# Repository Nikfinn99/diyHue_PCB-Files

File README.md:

# Moved to [Nikfinn99/PCB_Designs](https://github.com/Nikfinn99/PCB_Designs)
# in this new repo are also more Designs available

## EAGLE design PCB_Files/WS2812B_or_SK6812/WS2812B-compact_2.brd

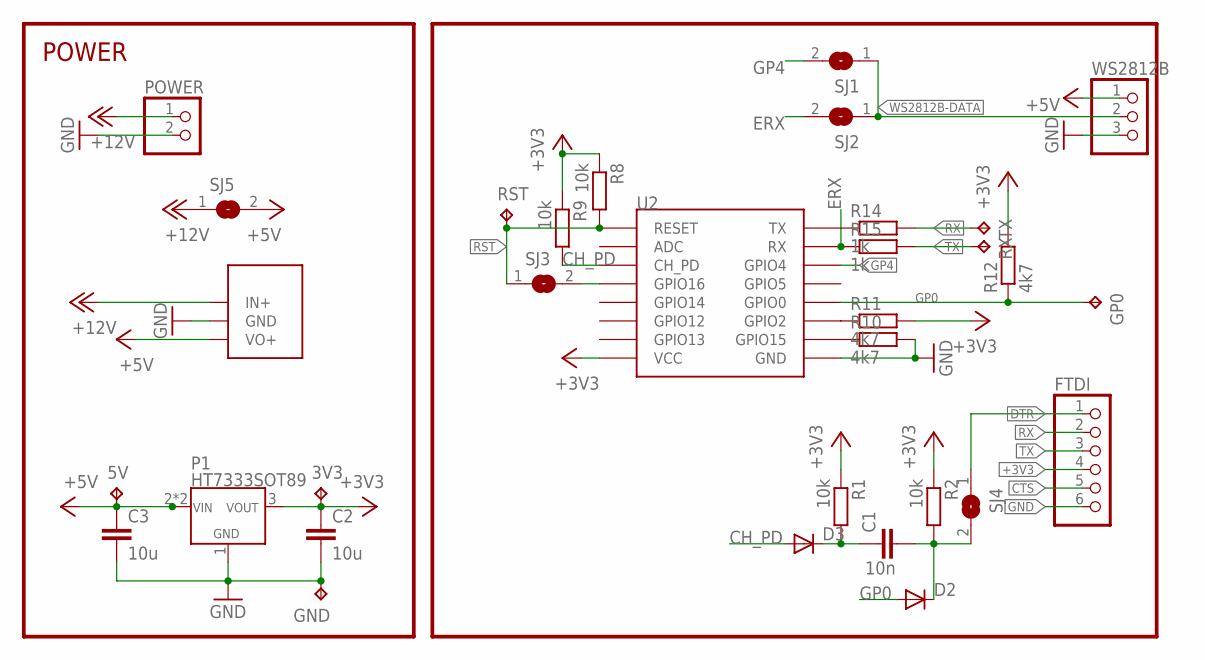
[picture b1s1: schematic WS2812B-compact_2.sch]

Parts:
3V3, 5V: TPB1,27; B1,27
C1: 10n; C0805
C2, C3: 10u; C0805
D2, D3: DIODE-MINIMELF; MINIMELF
FTDI: PINHD-1X06_2.54-S; 1X06-S
GND: TPB1,27; B1,27
GP0: TPB1,27; B1,27
P1: HT7333SOT89; SOT89
POWER: PINHD-1X2; 1X02
R1, R2, R8, R9: 10k; R0805
R10, R11, R12: 4k7; R0805
R14, R15: 1k; R0805
RST: TPB1,27; B1,27
RX: TPB1,27; B1,27
SJ1, SJ2, SJ3, SJ4, SJ5: SJ
TX: TPB1,27; B1,27
U2: ESP12SMD; ESP12-SMD
U$1: BUCK_CONVERTER_TE818_VAR
WS2812B: PINHD-1X03_2.54-S; 1X03-S

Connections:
+3V3: 3V3.TP, C2.1, FTDI.4, P1.3 (VOUT), R1.1, R2.1, R8.1, R9.1, R11.2, R12.2, U2.VCC
+5V: 5V.TP, C3.1, P1.2 (VIN), P1.2@1 (VIN), SJ5.2, U$1.VO+, WS2812B.1
+12V: POWER.1, SJ5.1, U$1.IN+
CH_PD: D3.A, R9.2, U2.CH_PD
CTS: FTDI.5
DTR: FTDI.1, SJ4.1
ERX: R15.1, SJ2.2, U2.RXD0 (RX)
GND: C2.2, C3.2, FTDI.6, GND.TP, P1.1 (GND), POWER.2, R10.2, U2.GND, U$1.GND, WS2812B.3
GP0: D2.A, GP0.TP, R12.1, U2.GPIO0
GP4: SJ1.2, U2.GPIO4
unnamed: C1.2, D2.C, R2.2, SJ4.2
unnamed: C1.1, D3.C, R1.2
unnamed: R10.1, U2.GPIO15
unnamed: R11.1, U2.GPIO2
unnamed: SJ3.2, U2.GPIO16
unnamed: R14.1, U2.TXD0 (TX)
RST: R8.2, RST.TP, SJ3.1, U2.RESET
RX: FTDI.2, R14.2, TX.TP
TX: FTDI.3, R15.2, RX.TP
WS2812B-DATA: SJ1.1, SJ2.1, WS2812B.2

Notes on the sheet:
POWER

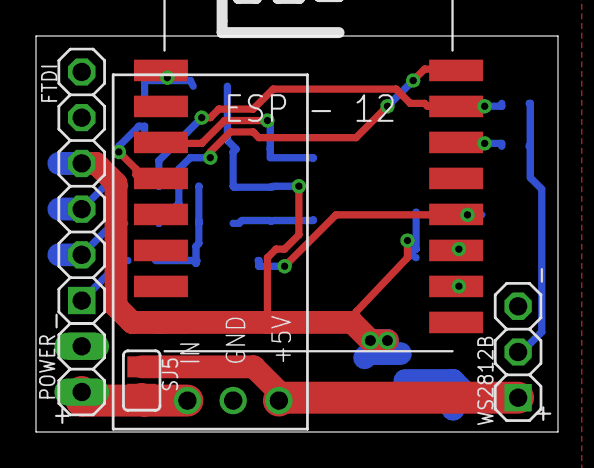
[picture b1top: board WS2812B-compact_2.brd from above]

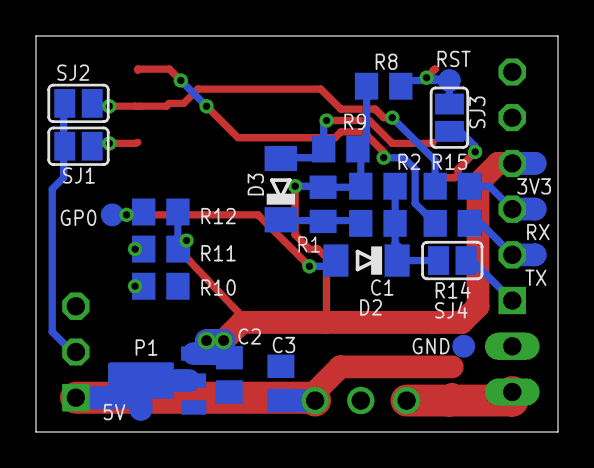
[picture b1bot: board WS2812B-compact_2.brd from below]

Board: 2 copper layers, 29.0 x 22.0 mm, 32 parts (26 on the bottom side), 19 nets.

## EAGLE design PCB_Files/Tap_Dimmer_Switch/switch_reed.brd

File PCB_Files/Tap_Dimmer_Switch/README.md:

## This design is currently under development

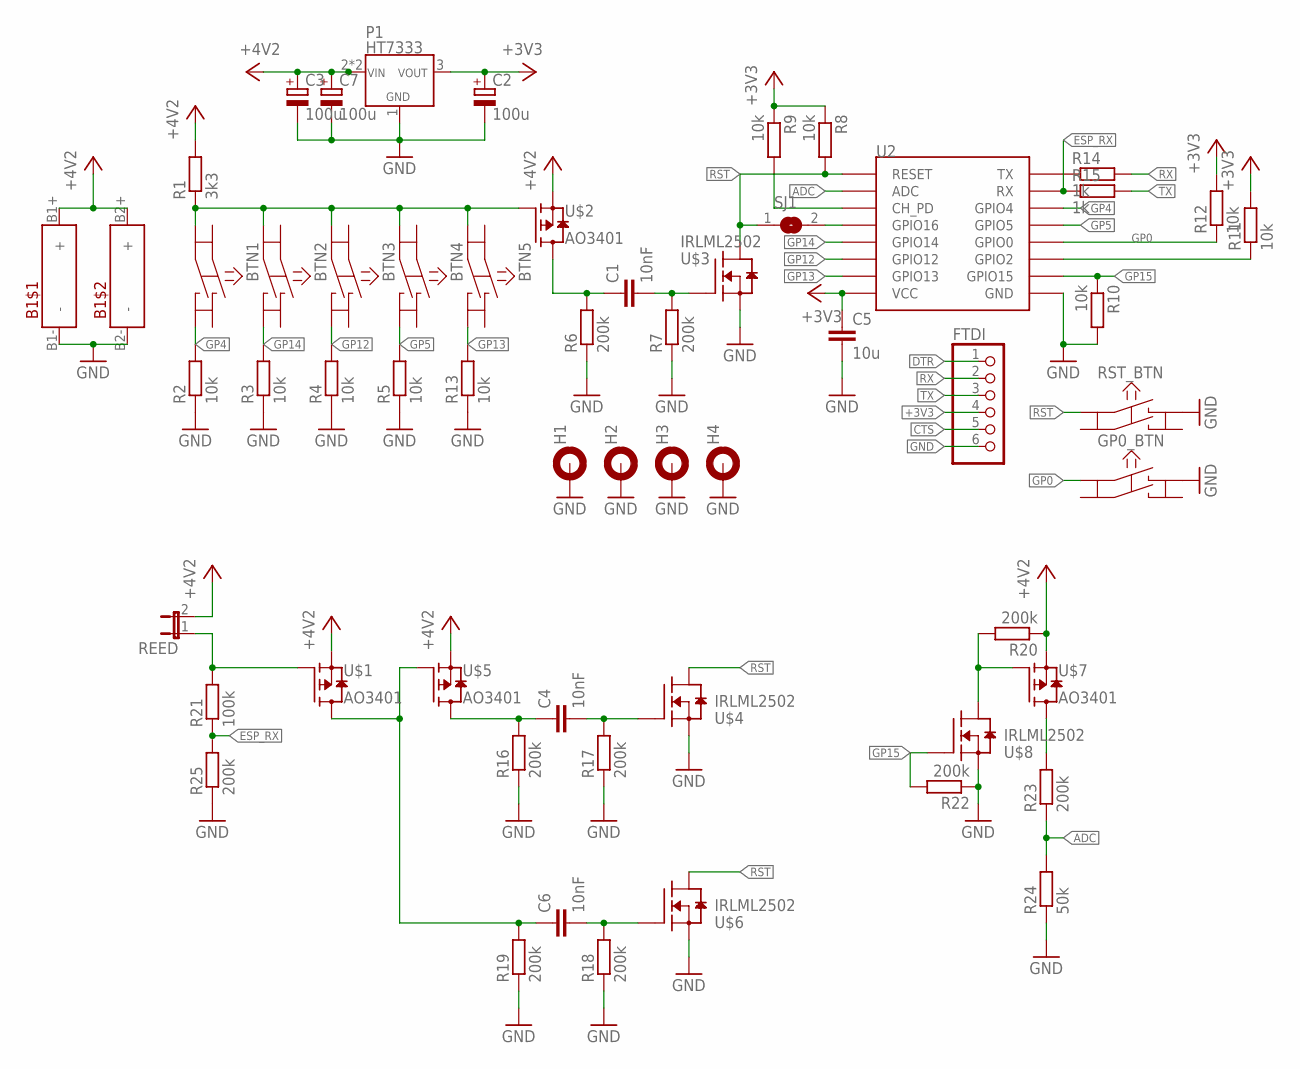
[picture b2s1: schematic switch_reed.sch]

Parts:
B1: 18650_2X; 18650_HOLDER
BTN1, BTN2, BTN3, BTN4, BTN5: KSM611A
C1, C4, C6: 10nF; C0805
C2, C3, C7: 100u; E5-8,5
C5: 10u; C1206
FTDI: PINHD-1X06_2.54-S; 1X06-S
GP0_BTN: KSM611A
H1, H2, H3, H4: MOUNT-PAD-ROUND3.2; 3,2-PAD
P1: HT7333; SOT89
R1: 3k3; R0805
R2, R3, R4, R5, R8, R9, R10, R11, R12, R13: 10k; R0805
R6, R7, R16, R17, R18, R19, R20, R22, R23, R25: 200k; R0805
R14, R15: 1k; R0805
R21: 100k; R0805
R24: 50k; R0805
REED: JP1E; JP1
RST_BTN: KSM611A
SJ1: SJ
U2: ESP12SMD; ESP12-SMD
U$1, U$2, U$5, U$7: AO3401; SOT23
U$3, U$4, U$6, U$8: IRLML2502; SOT23

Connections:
+3V3: C2.+, C5.1, FTDI.4, P1.3 (VOUT), R8.1, R9.1, R11.2, R12.2, U2.VCC
+5V: B1.B1+ (+), B1.B2+ (+), C3.+, C7.+, P1.2 (VIN), P1.2@1 (VIN), R1.2, R20.1, REED.2, U$1.2 (S), U$2.2 (S), U$5.2 (S), U$7.2 (S)
ADC: R23.1, R24.2, U2.ADC
CTS: FTDI.5
DTR: FTDI.1
ESP_RX: R15.1, R21.1, R25.2, U2.RXD0 (RX)
GND: B1.B1- (-), B1.B2- (-), C2.-, C3.-, C5.2, C7.-, FTDI.6, GP0_BTN.B, H1.B3,2, H2.B3,2, H3.B3,2, H4.B3,2, P1.1 (GND), R2.1, R3.1, R4.1, R5.1, R6.1, R7.1, R10.2, R13.1, R16.1, R17.1, R18.1, R19.1, R22.1, R24.1, R25.1, RST_BTN.B, U2.GND, U$3.2 (S), U$4.2 (S), U$6.2 (S), U$8.2 (S)
GP0: GP0_BTN.A, R12.1, U2.GPIO0
GP4: BTN1.D, R2.2, U2.GPIO4
GP5: BTN4.D, R5.2, U2.GPIO5
GP12: BTN3.D, R4.2, U2.GPIO12
GP13: BTN5.D, R13.2, U2.GPIO13
GP14: BTN2.D, R3.2, U2.GPIO14
GP15: R10.1, R22.2, U2.GPIO15, U$8.1 (G)
unnamed: SJ1.2, U2.GPIO16
unnamed: R9.2, U2.CH_PD
unnamed: C1.2, R7.2, U$3.1 (G)
unnamed: R11.1, U2.GPIO2
unnamed: R14.1, U2.TXD0 (TX)
unnamed: C1.1, R6.2, U$2.3 (D)
unnamed: BTN1.C, BTN2.C, BTN3.C, BTN4.C, BTN5.C, R1.1, U$2.1 (G)
unnamed: C6.1, R19.2, U$1.3 (D), U$5.1 (G)
unnamed: C4.1, R16.2, U$5.3 (D)
unnamed: C4.2, R17.2, U$4.1 (G)
unnamed: C6.2, R18.2, U$6.1 (G)
unnamed: R20.2, U$7.1 (G), U$8.3 (D)
unnamed: R23.2, U$7.3 (D)
unnamed: R21.2, REED.1, U$1.1 (G)
RST: R8.2, RST_BTN.A, SJ1.1, U2.RESET, U$3.3 (D), U$4.3 (D), U$6.3 (D)
RX: FTDI.2, R14.2
TX: FTDI.3, R15.2

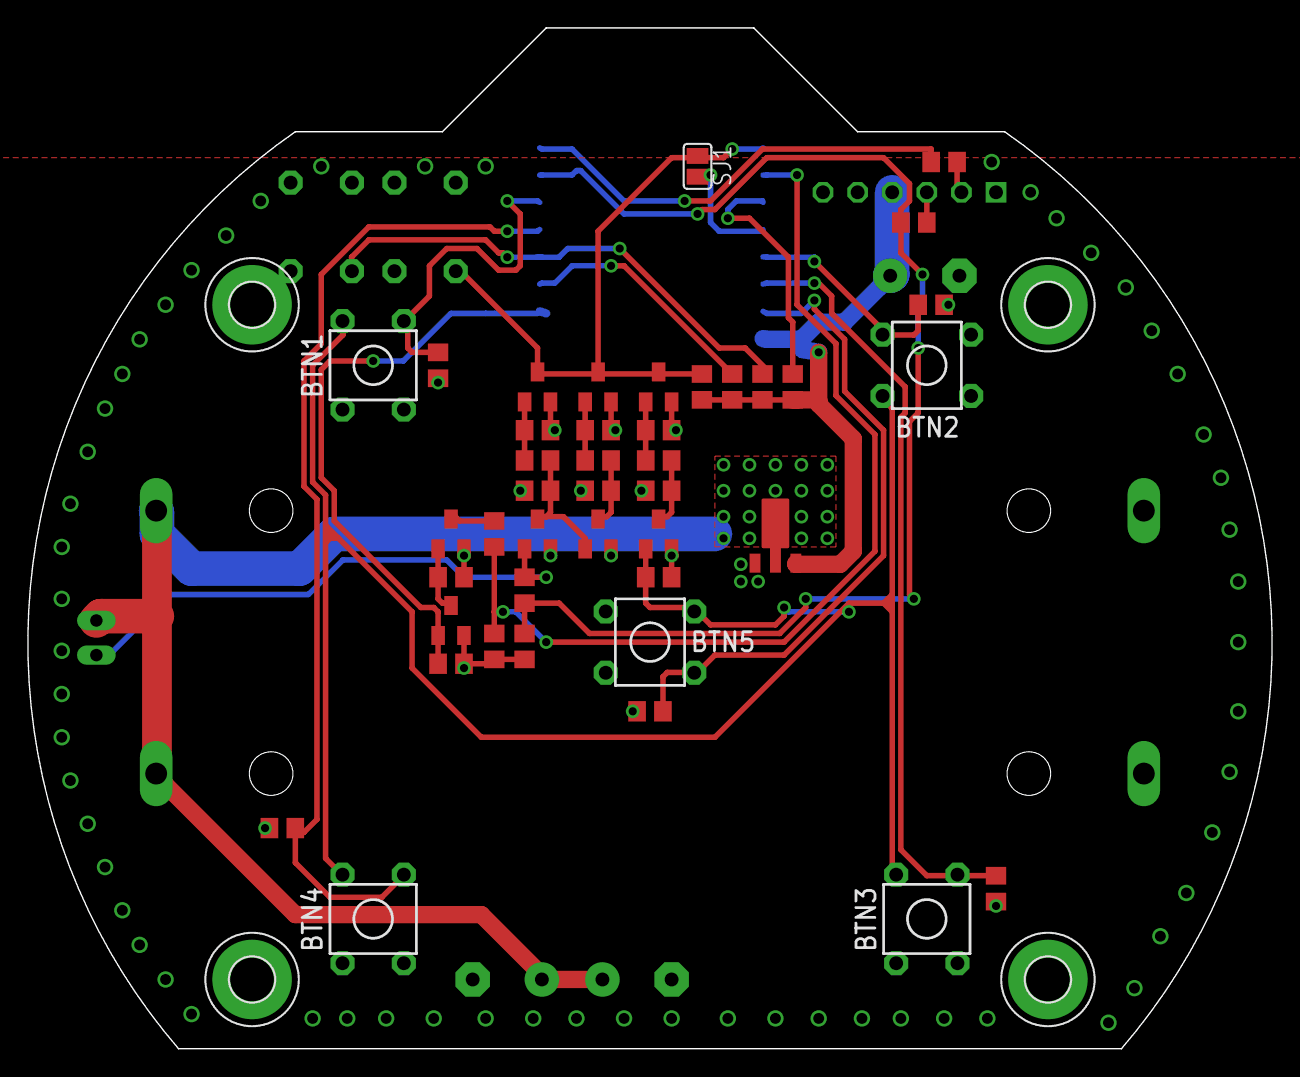
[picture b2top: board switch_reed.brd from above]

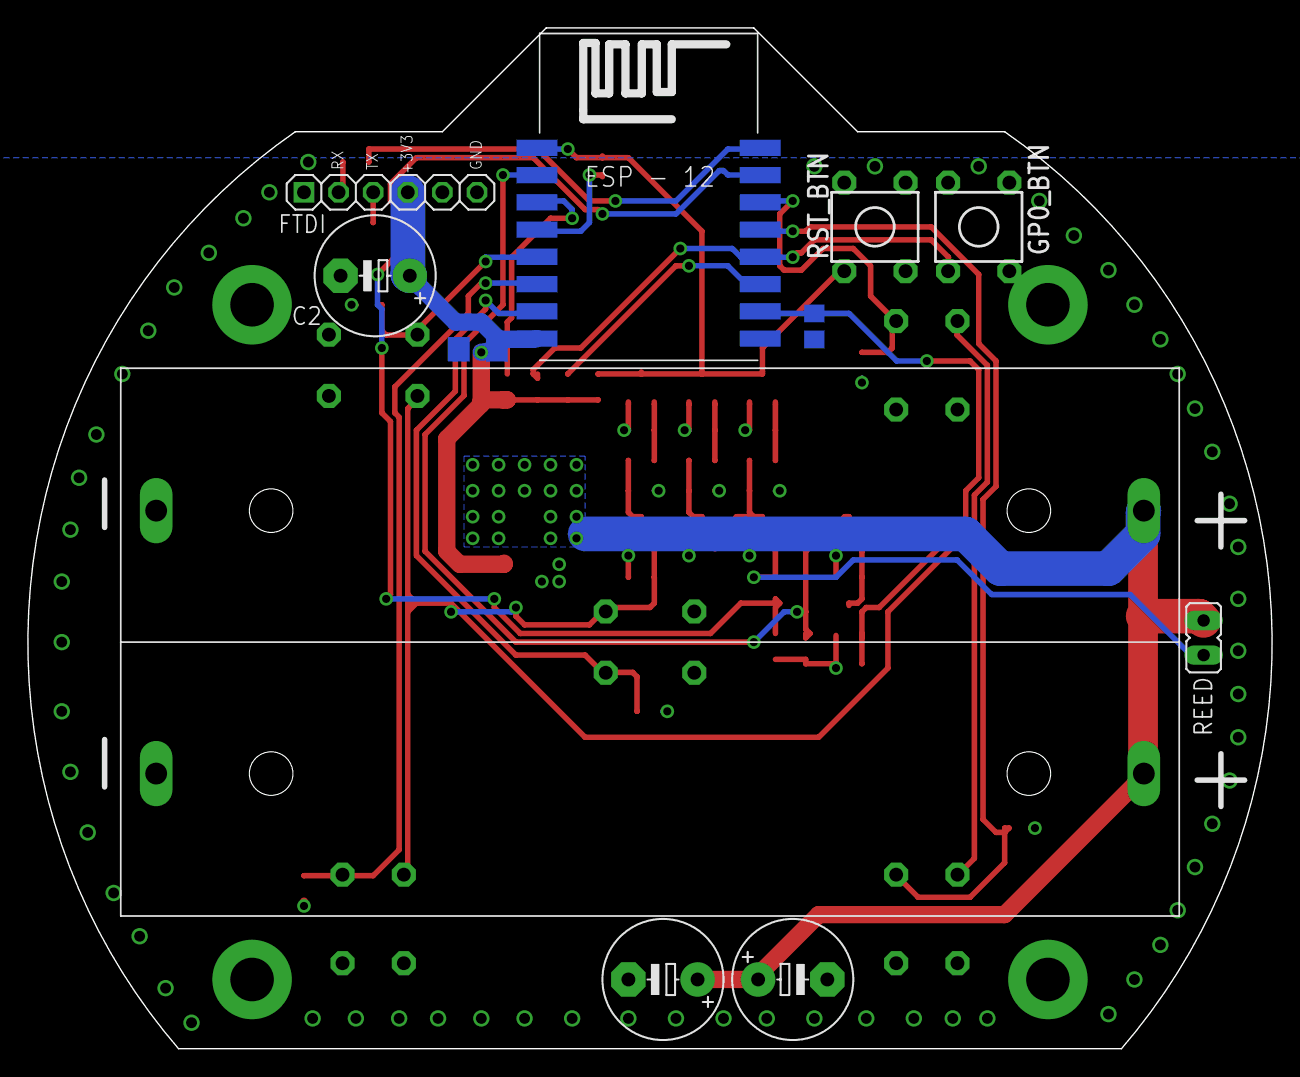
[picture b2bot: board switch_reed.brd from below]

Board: 2 copper layers, 91.3 x 74.9 mm, 57 parts (11 on the bottom side), 29 nets.

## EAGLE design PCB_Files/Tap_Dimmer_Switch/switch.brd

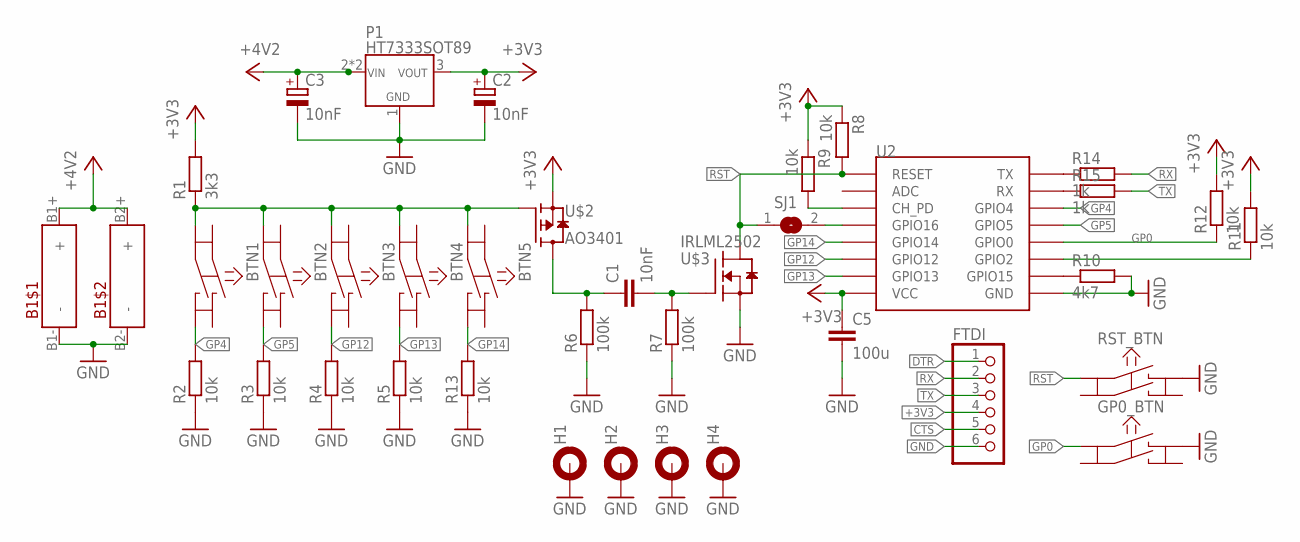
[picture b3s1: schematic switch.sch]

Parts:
B1: 18650_2X; 18650_HOLDER
BTN1, BTN2, BTN3, BTN4, BTN5: KSM611A
C1: 10nF; C025-025X050
C2, C3: 10nF; E5-8,5
C5: 100u; C1206
FTDI: PINHD-1X06_2.54-S; 1X06-S
GP0_BTN: KSM611A
H1, H2, H3, H4: MOUNT-PAD-ROUND3.2; 3,2-PAD
P1: HT7333SOT89; SOT89
R1: 3k3; MULTI_RESISTOR
R2, R3, R4, R5, R8, R9, R11, R12, R13: 10k; MULTI_RESISTOR
R6, R7: 100k; MULTI_RESISTOR
R10: 4k7; MULTI_RESISTOR
R14, R15: 1k; MULTI_RESISTOR
RST_BTN: KSM611A
SJ1: SJ
U2: ESP12SMD; ESP12-SMD
U$2: AO3401; SOT23
U$3: IRLML2502; SOT23

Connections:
+3V3: C2.+, C5.1, FTDI.4, P1.3 (VOUT), R1.2@1 (2), R1.2@2 (2), R8.1@1 (1), R8.1@2 (1), R9.1@1 (1), R9.1@2 (1), R11.2@1 (2), R11.2@2 (2), R12.2@1 (2), R12.2@2 (2), U2.VCC, U$2.2 (S)
+5V: B1.B1+ (+), B1.B2+ (+), C3.+, P1.2 (VIN), P1.2@1 (VIN)
CTS: FTDI.5
DTR: FTDI.1
GND: B1.B1- (-), B1.B2- (-), C2.-, C3.-, C5.2, FTDI.6, GP0_BTN.B, H1.B3,2, H2.B3,2, H3.B3,2, H4.B3,2, P1.1 (GND), R2.1@1 (1), R2.1@2 (1), R3.1@1 (1), R3.1@2 (1), R4.1@1 (1), R4.1@2 (1), R5.1@1 (1), R5.1@2 (1), R6.1@1 (1), R6.1@2 (1), R7.1@1 (1), R7.1@2 (1), R10.2@1 (2), R10.2@2 (2), R13.1@1 (1), R13.1@2 (1), RST_BTN.B, U2.GND, U$3.2 (S)
GP0: GP0_BTN.A, R12.1@1 (1), R12.1@2 (1), U2.GPIO0
GP4: BTN1.D, R2.2@1 (2), R2.2@2 (2), U2.GPIO4
GP5: BTN2.D, R3.2@1 (2), R3.2@2 (2), U2.GPIO5
GP12: BTN3.D, R4.2@1 (2), R4.2@2 (2), U2.GPIO12
GP13: BTN4.D, R5.2@1 (2), R5.2@2 (2), U2.GPIO13
GP14: BTN5.D, R13.2@1 (2), R13.2@2 (2), U2.GPIO14
unnamed: SJ1.2, U2.GPIO16
unnamed: R9.2@1 (2), R9.2@2 (2), U2.CH_PD
unnamed: C1.2, R7.2@1 (2), R7.2@2 (2), U$3.1 (G)
unnamed: R10.1@1 (1), R10.1@2 (1), U2.GPIO15
unnamed: R11.1@1 (1), R11.1@2 (1), U2.GPIO2
unnamed: R14.1@1 (1), R14.1@2 (1), U2.TXD0 (TX)
unnamed: C1.1, R6.2@1 (2), R6.2@2 (2), U$2.3 (D)
unnamed: BTN1.C, BTN2.C, BTN3.C, BTN4.C, BTN5.C, R1.1@1 (1), R1.1@2 (1), U$2.1 (G)
unnamed: R15.1@1 (1), R15.1@2 (1), U2.RXD0 (RX)
RST: R8.2@1 (2), R8.2@2 (2), RST_BTN.A, SJ1.1, U2.RESET, U$3.3 (D)
RX: FTDI.2, R14.2@1 (2), R14.2@2 (2)
TX: FTDI.3, R15.2@1 (2), R15.2@2 (2)

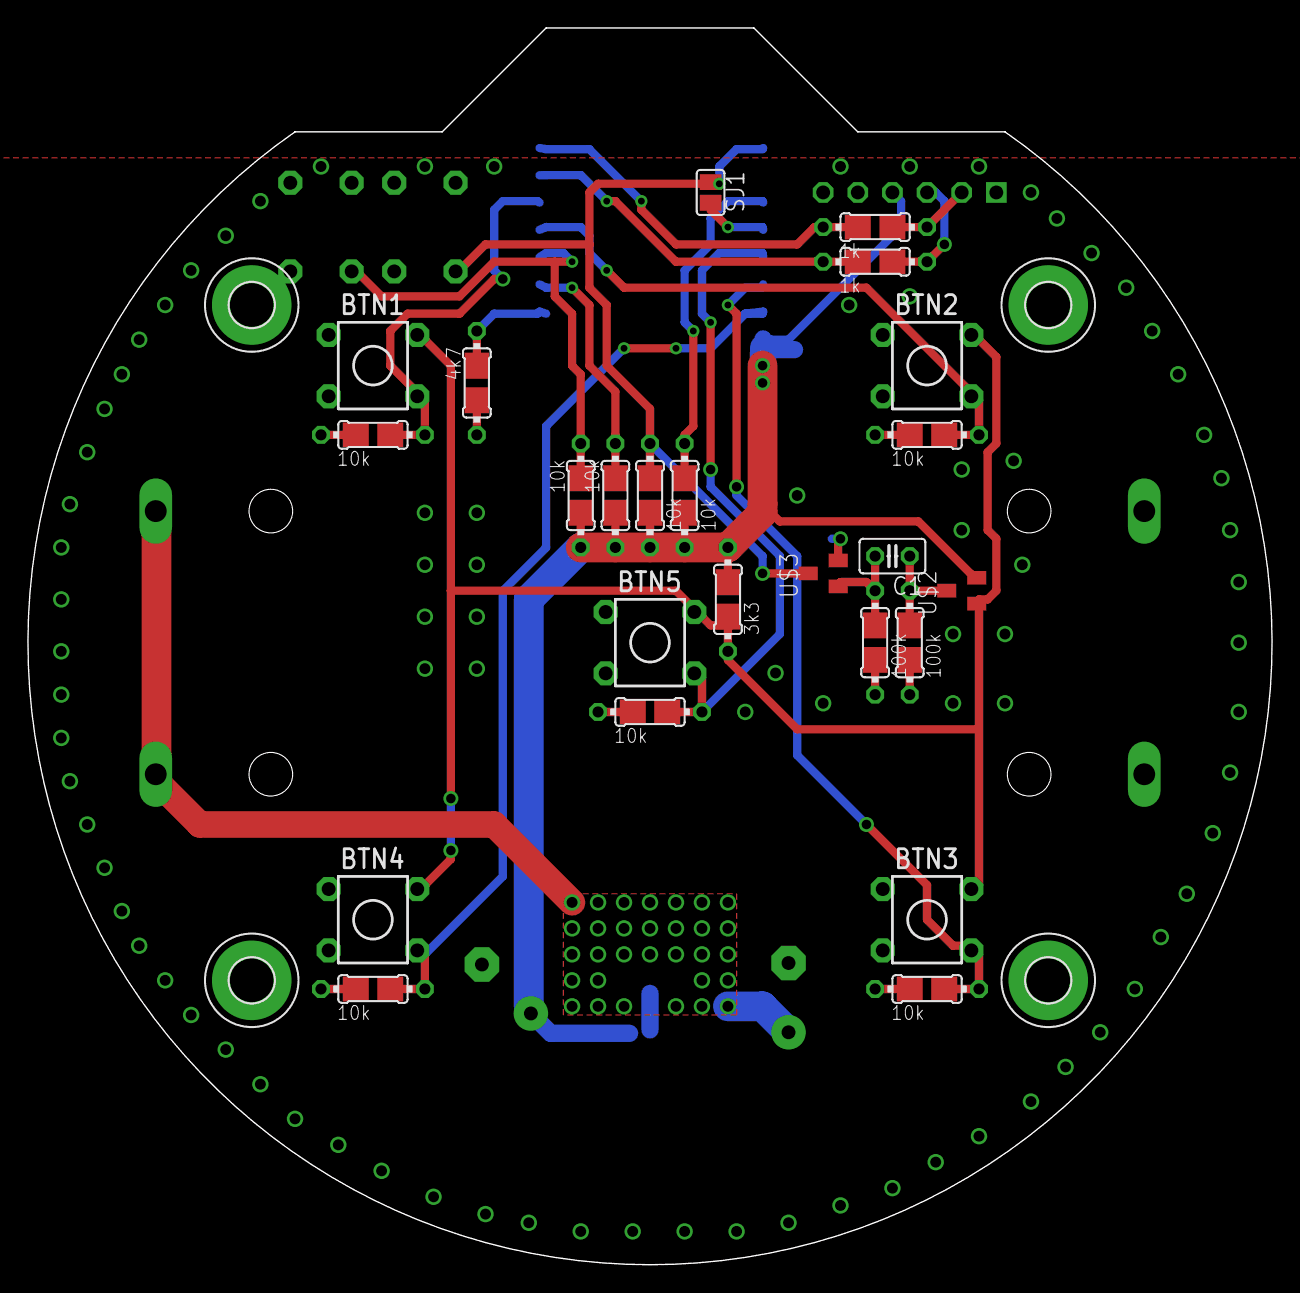
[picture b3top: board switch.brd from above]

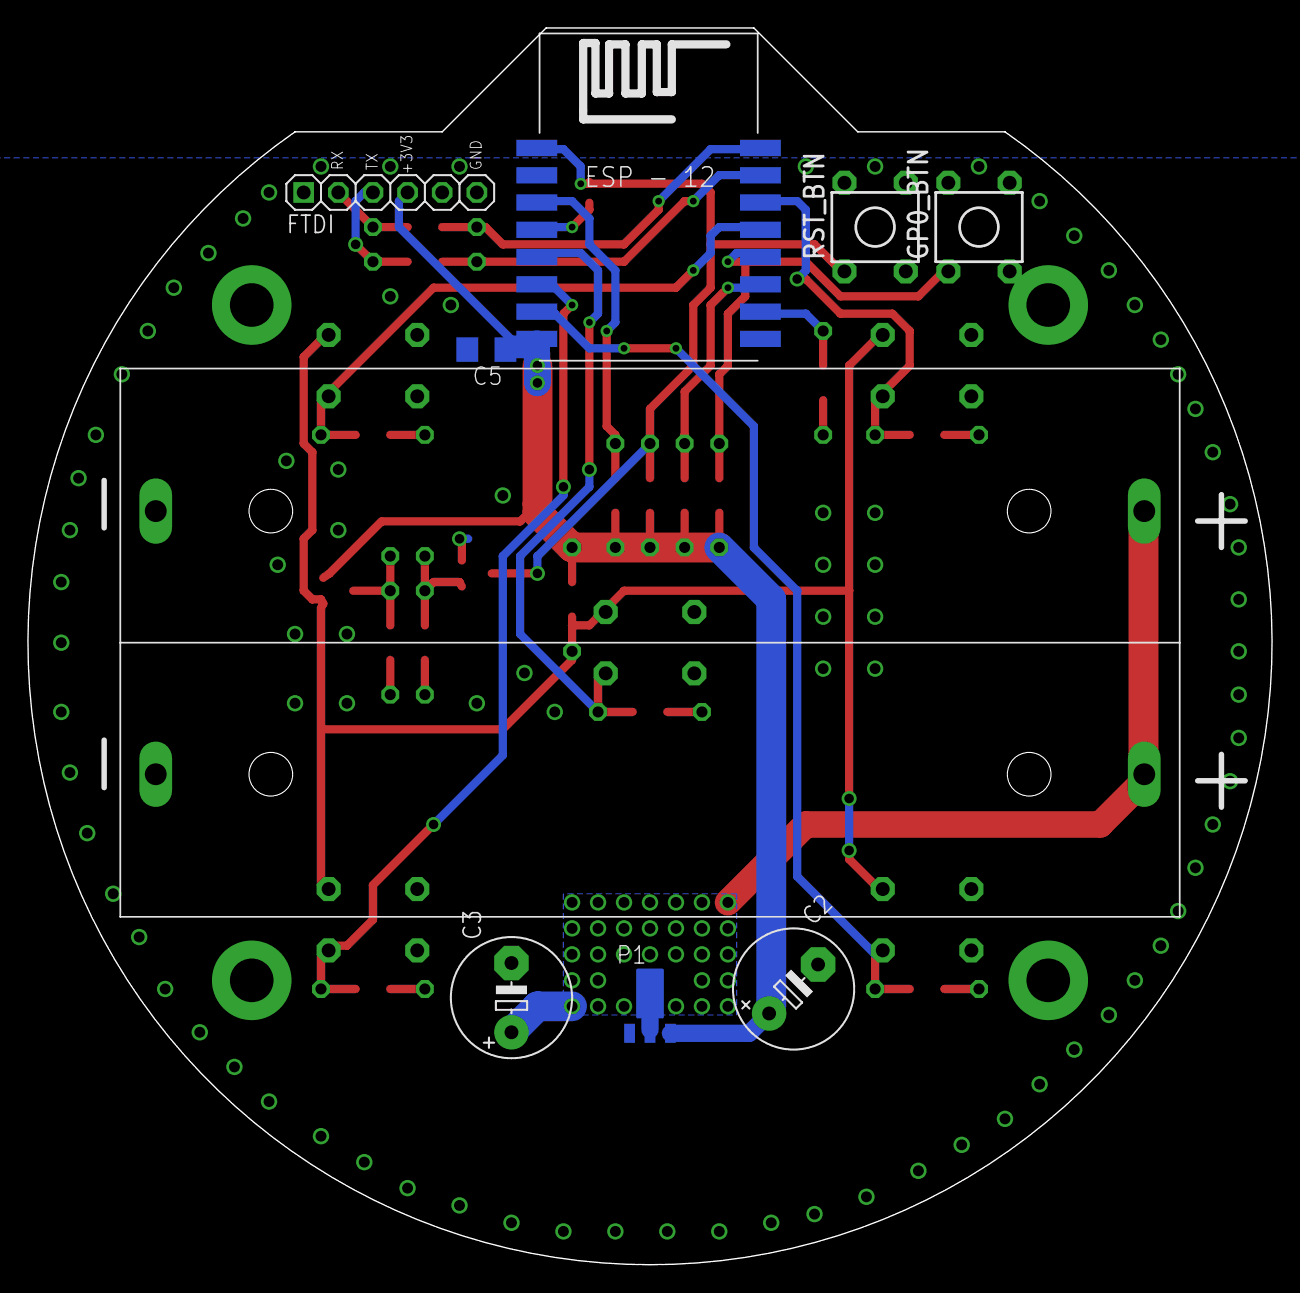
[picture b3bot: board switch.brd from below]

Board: 2 copper layers, 91.2 x 90.7 mm, 37 parts (9 on the bottom side), 21 nets.

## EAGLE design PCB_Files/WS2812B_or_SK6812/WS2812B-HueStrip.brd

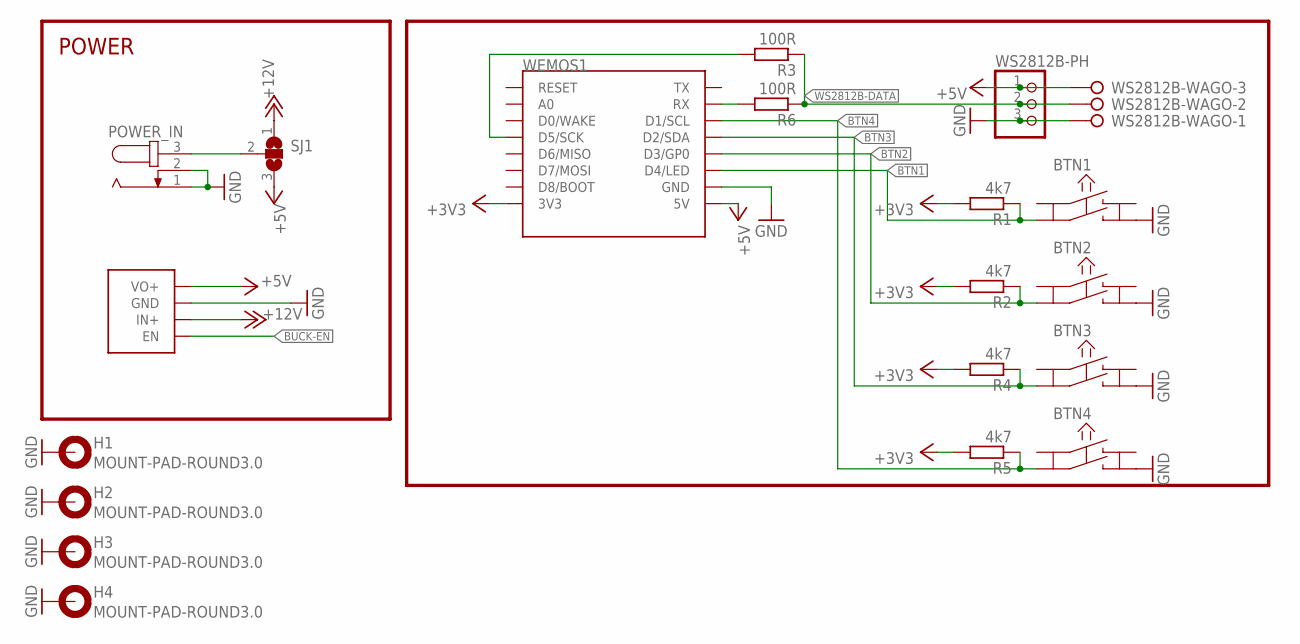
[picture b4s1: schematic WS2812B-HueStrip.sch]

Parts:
BTN1, BTN2, BTN3, BTN4: KSM611A
H1, H2, H3, H4: MOUNT-PAD-ROUND3.0; 3,0-PAD
POWER_IN: RAPC7120; RAPC712
R1, R2, R4, R5: 4k7; MULTI_RESISTOR
R3, R6: 100R; MULTI_RESISTOR
SJ1: SJ2WW; SJ_2W
U$1: BUCK_CONVERTER_TE818
WEMOS1: WEMOS-D1-MINI
WS2812B-PH: PINHD-1X03_2.54-S; 1X03-S
WS2812B-WAGO: W237-3E

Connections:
+3V3: R1.2@1 (2), R1.2@2 (2), R2.2@1 (2), R2.2@2 (2), R4.2@1 (2), R4.2@2 (2), R5.2@1 (2), R5.2@2 (2), WEMOS1.3V3
+5V: SJ1.3, U$1.VO+, WEMOS1.5V, WS2812B-PH.1, WS2812B-WAGO.3
+12V: SJ1.1, U$1.IN+
BTN1: BTN1.C, R1.1@1 (1), R1.1@2 (1), WEMOS1.D4 (D4/LED)
BTN2: BTN2.C, R2.1@1 (1), R2.1@2 (1), WEMOS1.D3 (D3/GP0)
BTN3: BTN3.C, R4.1@1 (1), R4.1@2 (1), WEMOS1.D2 (D2/SDA)
BTN4: BTN4.C, R5.1@1 (1), R5.1@2 (1), WEMOS1.D1 (D1/SCL)
BUCK-EN: U$1.EN
GND: BTN1.D, BTN2.D, BTN3.D, BTN4.D, H1.B3,0, H2.B3,0, H3.B3,0, H4.B3,0, POWER_IN.1, POWER_IN.2, U$1.GND, WEMOS1.GND, WS2812B-PH.3, WS2812B-WAGO.1
unnamed: POWER_IN.3, SJ1.2
unnamed: R3.2@1 (2), R3.2@2 (2), WEMOS1.D5 (D5/SCK)
unnamed: R6.2@1 (2), R6.2@2 (2), WEMOS1.RX
WS2812B-DATA: R3.1@1 (1), R3.1@2 (1), R6.1@1 (1), R6.1@2 (1), WS2812B-PH.2, WS2812B-WAGO.2

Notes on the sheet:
POWER

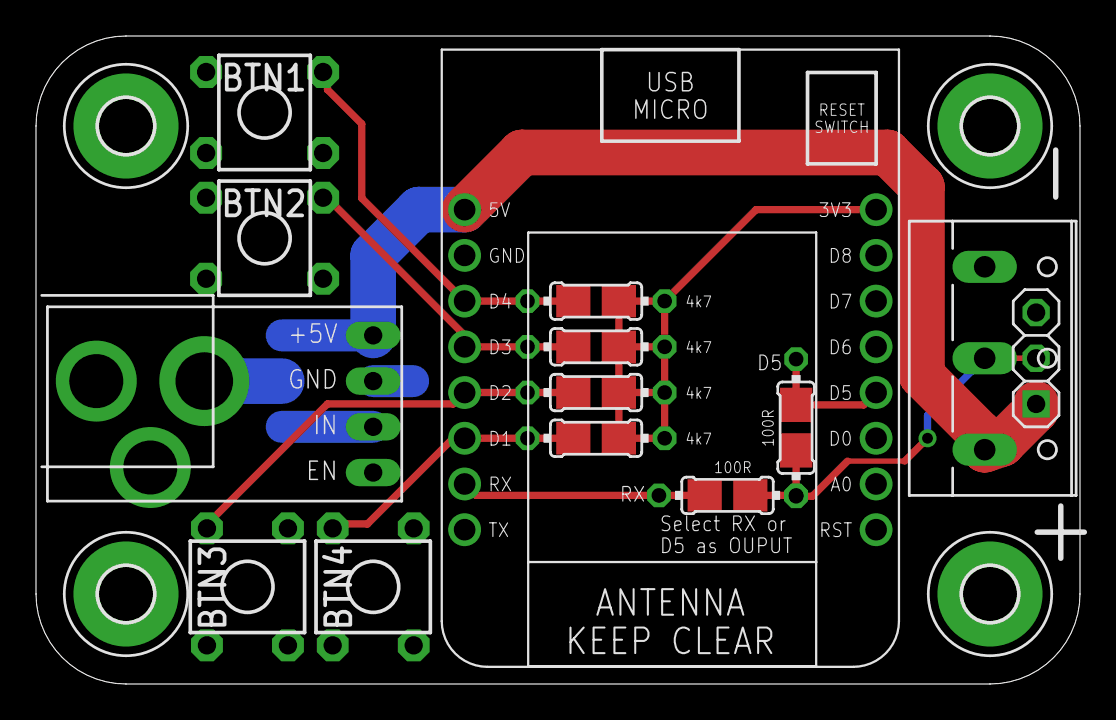
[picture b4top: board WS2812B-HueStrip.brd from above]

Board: 2 copper layers, 58.0 x 36.0 mm, 20 parts (1 on the bottom side), 12 nets.

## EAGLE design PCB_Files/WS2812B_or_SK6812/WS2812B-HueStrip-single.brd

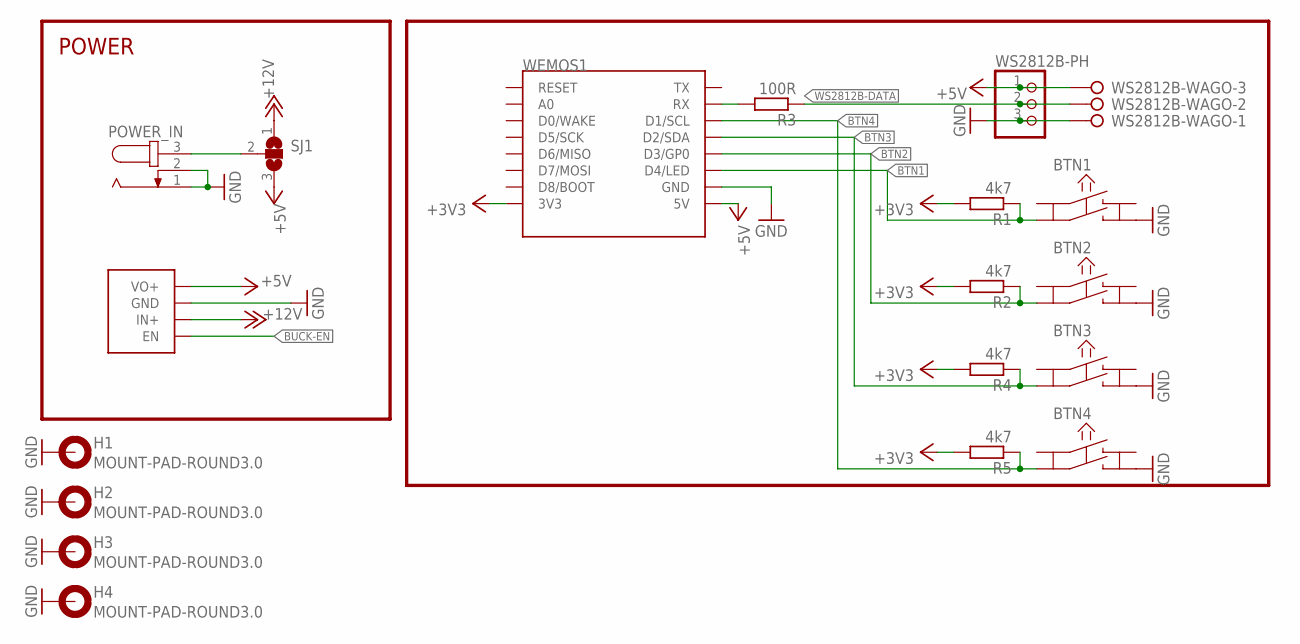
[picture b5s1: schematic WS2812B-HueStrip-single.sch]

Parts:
BTN1, BTN2, BTN3, BTN4: KSM611A
H1, H2, H3, H4: MOUNT-PAD-ROUND3.0; 3,0-PAD
POWER_IN: RAPC7120; RAPC712
R1, R2, R4, R5: 4k7; 0204/7
R3: 100R; 0204/7
SJ1: SJ2WW; SJ_2W
U$1: BUCK_CONVERTER_TE818
WEMOS1: WEMOS-D1-MINI
WS2812B-PH: PINHD-1X03_2.54-S; 1X03-S
WS2812B-WAGO: W237-3E

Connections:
+3V3: R1.2, R2.2, R4.2, R5.2, WEMOS1.3V3
+5V: SJ1.3, U$1.VO+, WEMOS1.5V, WS2812B-PH.1, WS2812B-WAGO.3
+12V: SJ1.1, U$1.IN+
BTN1: BTN1.C, R1.1, WEMOS1.D4 (D4/LED)
BTN2: BTN2.C, R2.1, WEMOS1.D3 (D3/GP0)
BTN3: BTN3.C, R4.1, WEMOS1.D2 (D2/SDA)
BTN4: BTN4.C, R5.1, WEMOS1.D1 (D1/SCL)
BUCK-EN: U$1.EN
GND: BTN1.D, BTN2.D, BTN3.D, BTN4.D, H1.B3,0, H2.B3,0, H3.B3,0, H4.B3,0, POWER_IN.1, POWER_IN.2, U$1.GND, WEMOS1.GND, WS2812B-PH.3, WS2812B-WAGO.1
unnamed: POWER_IN.3, SJ1.2
unnamed: R3.2, WEMOS1.RX
WS2812B-DATA: R3.1, WS2812B-PH.2, WS2812B-WAGO.2

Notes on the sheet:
POWER

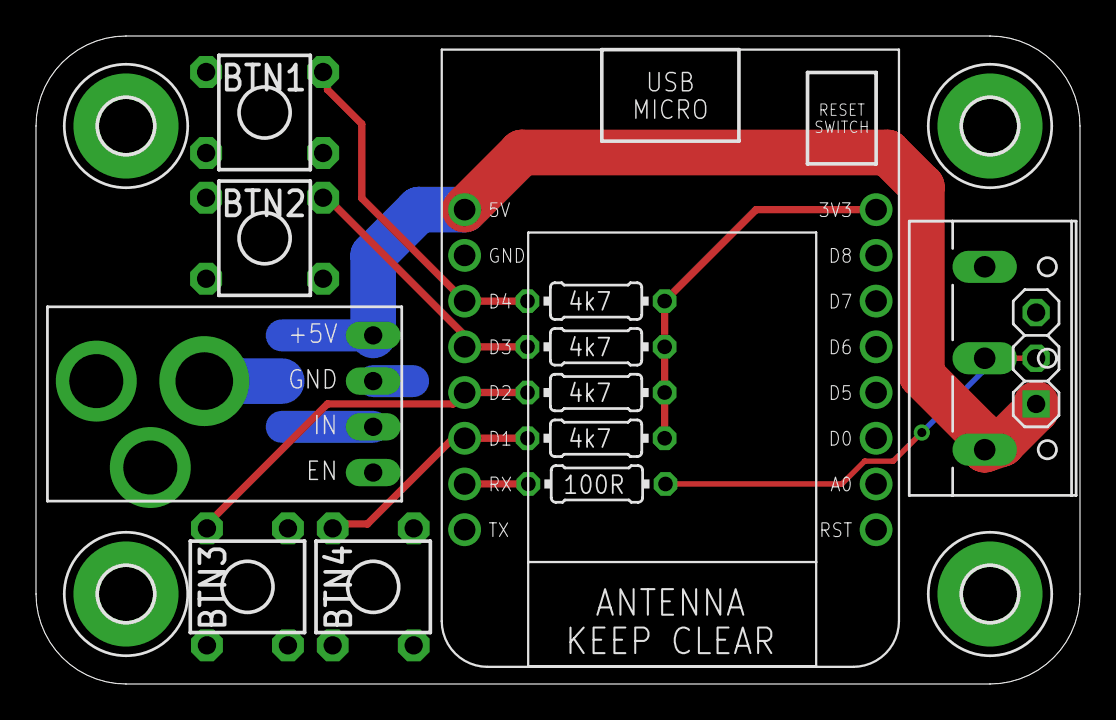
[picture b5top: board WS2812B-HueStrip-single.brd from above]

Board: 2 copper layers, 58.0 x 36.0 mm, 19 parts (1 on the bottom side), 11 nets.

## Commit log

2018-09-25 added rendered images from jlcpcb
2018-09-25 add images
2018-09-25 move images to table
2018-09-25 add header to table
2018-09-25 updated images
2018-09-25 removed old gerbers
2018-09-25 remove unneccesary bstop
2018-09-25 remove notes
2018-09-25 fixed design
2018-12-01 Updated gerber Files to fix breaking bug
    the original design had some errors that were only found after they were ordered. Those bugs hab been fixed.
    Also there were new pictures exported of the design and schematic
2018-12-01 add new images and changelog
2018-12-23 Created PCB for Tap/Dimmer Switch
2018-12-28 Added Design with additional reed (magnet) sensor
    this version is not entirely finished and has to be improved upon
2018-12-30 upload images for pwm driver
2018-12-30 update Link to diyHue
2018-12-30 add bottom image
2018-12-30 add bottom image with text
2018-12-30 Add Readme doc for pwm driver
2018-12-30 add comment for voltage reg
2018-12-30 development
2018-12-30 fix error
2019-01-01 remove warning
2019-01-06 updated gerber
2019-01-11 add compact ws2812b design (untested)
2019-01-23 created additional compact design of ws2812b module
    this new design features smaller footprint, but the esp module ist partially outside the board, which will result in better wifi connection.
    additionally the footprint of the HT7333 has been fixed as previously it had used the wrong package.
2019-05-11 depreciate Repo: moved to Nikfinn99/PCB_Designs
2019-05-11 remove old files
